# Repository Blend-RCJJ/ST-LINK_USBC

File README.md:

# ST-LINK_USBC

ST-LINKのUSB-C版です。STM32チップはNucleoから剥がして作ってください。

ライセンスはCC BY-NC-SA 4.0でお願いします。

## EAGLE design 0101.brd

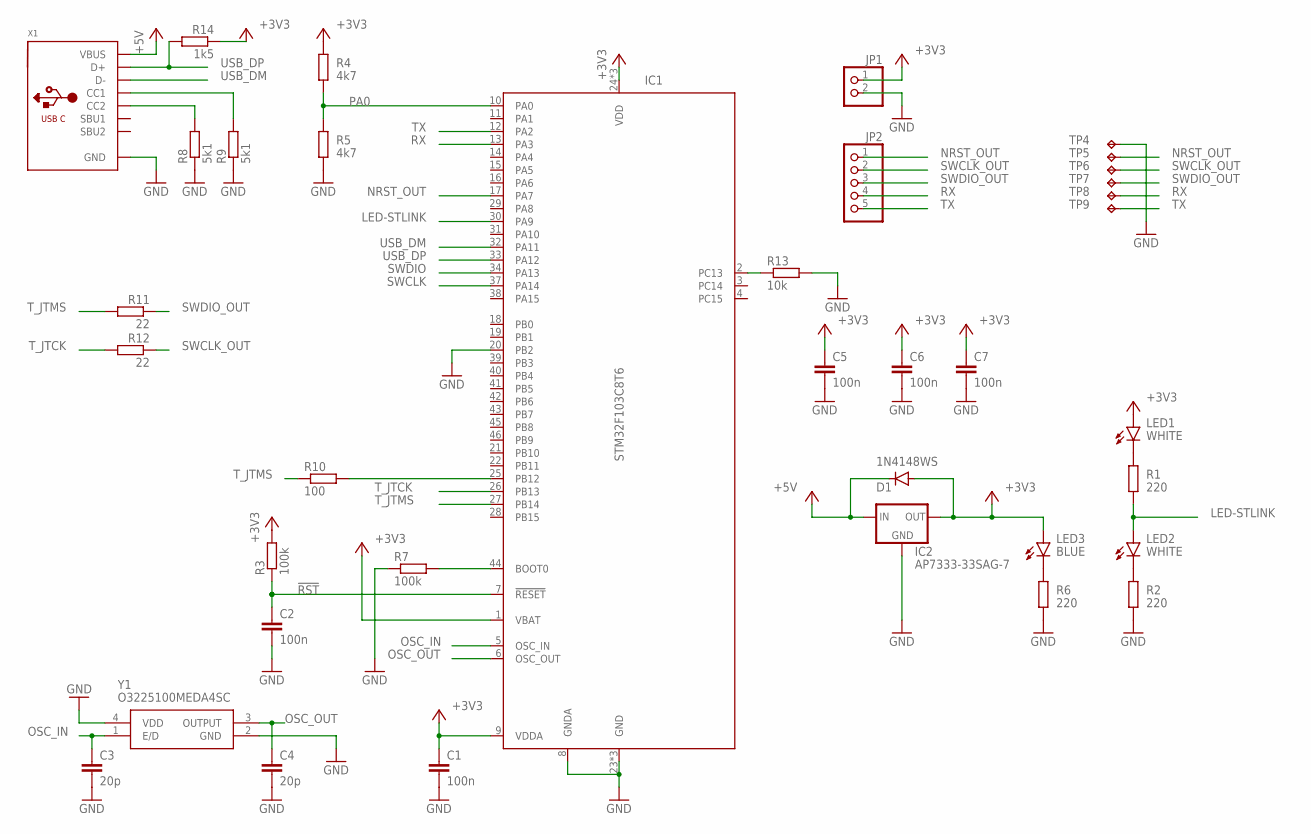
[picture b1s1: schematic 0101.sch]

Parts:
C1, C2, C5, C6, C7: 100n; C0402
C3, C4: 20p; C0402
D1: 1N4148WS; SOD323-R
IC1: STM32F103C8T6; QFP48-7X7-0.5
IC2: AP7333-33SAG-7; SOT23
JP1: PINHD-1X2; 1X02
JP2: PINHD-1X5; 1X05
LED1, LED2: WHITE; CHIP-LED0603
LED3: BLUE; CHIP-LED0603
R1, R2, R6: 220; R0402
R3, R7: 100k; R0402
R4, R5: 4k7; R0402
R8, R9: 5k1; R0402
R10: 100; R0402
R11, R12: 22; R0402
R13: 10k; R0402
R14: 1k5; R0402
TP4: TPTP10SQ; TP10SQ
TP5, TP6, TP7, TP8, TP9: TPTP10R; TP10R
X1: USB_C; USB_C_CUSB31-CFM2AX-01-X
Y1: O3225100MEDA4SC

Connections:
!RST: C2.1, IC1.7 (!RESET), R3.1
+3V3: C1.1, C5.1, C6.1, C7.1, D1.A, IC1.1 (VBAT), IC1.9 (VDDA), IC1.24 (VDD), IC1.36 (VDD), IC1.48 (VDD), IC2.2 (OUT), JP1.1, LED1.A, LED3.A, R3.2, R4.2, R14.1
+5V: D1.C, IC2.3 (IN), X1.A4B9 (VBUS), X1.B4A9 (VBUS)
GND: C1.2, C2.2, C3.2, C4.2, C5.2, C6.2, C7.2, IC1.8 (GNDA), IC1.20 (PB2), IC1.23 (GND), IC1.35 (GND), IC1.47 (GND), IC2.1 (GND), JP1.2, R2.1, R5.1, R6.1, R7.1, R8.1, R9.1, R13.2, TP4.TP, X1.A1B12 (GND), X1.B1A12 (GND), Y1.2 (GND), Y1.4 (VDD)
LED-STLINK: IC1.30 (PA9), LED2.A, R1.1
unnamed: IC1.2 (PC13), R13.1
unnamed: LED2.C, R2.2
unnamed: LED3.C, R6.2
unnamed: IC1.44 (BOOT0), R7.2
unnamed: LED1.C, R1.2
unnamed: R9.2, X1.A5 (CC1)
unnamed: R8.2, X1.B5 (CC2)
unnamed: IC1.25 (PB12), R10.2
NRST_OUT: IC1.17 (PA7), JP2.1, TP5.TP
OSC_IN: C3.1, IC1.5 (OSC_IN), Y1.1 (E/D)
OSC_OUT: C4.1, IC1.6 (OSC_OUT), Y1.3 (OUTPUT)
PA0: IC1.10 (PA0), R4.1, R5.2
RX: IC1.13 (PA3), JP2.4, TP8.TP
SWCLK: IC1.37 (PA14)
SWCLK_OUT: JP2.2, R12.1, TP6.TP
SWDIO: IC1.34 (PA13)
SWDIO_OUT: JP2.3, R11.1, TP7.TP
TX: IC1.12 (PA2), JP2.5, TP9.TP
T_JTCK: IC1.26 (PB13), R12.2
T_JTMS: IC1.27 (PB14), R10.1, R11.2
USB_DM: IC1.32 (PA11), X1.A7 (D-), X1.B7 (D-)
USB_DP: IC1.33 (PA12), R14.2, X1.A6 (D+), X1.B6 (D+)

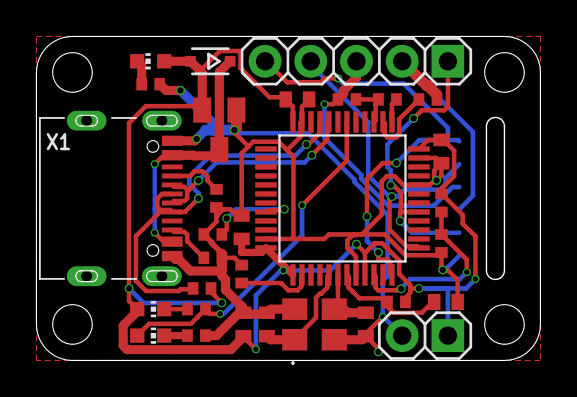
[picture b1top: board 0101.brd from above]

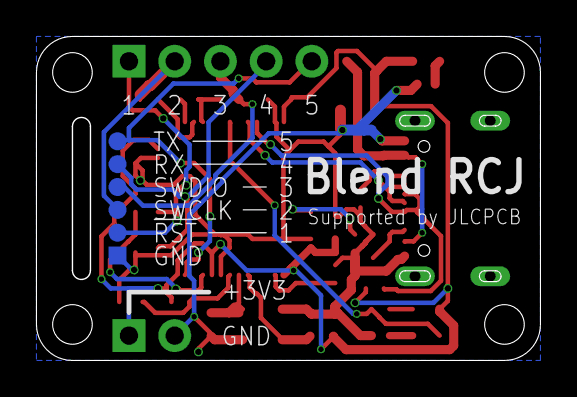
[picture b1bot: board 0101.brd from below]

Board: 2 copper layers, 28.0 x 18.0 mm, 37 parts (6 on the bottom side), 25 nets.

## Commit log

2022-09-20 基板データです
2022-09-20 Create LICENSE
